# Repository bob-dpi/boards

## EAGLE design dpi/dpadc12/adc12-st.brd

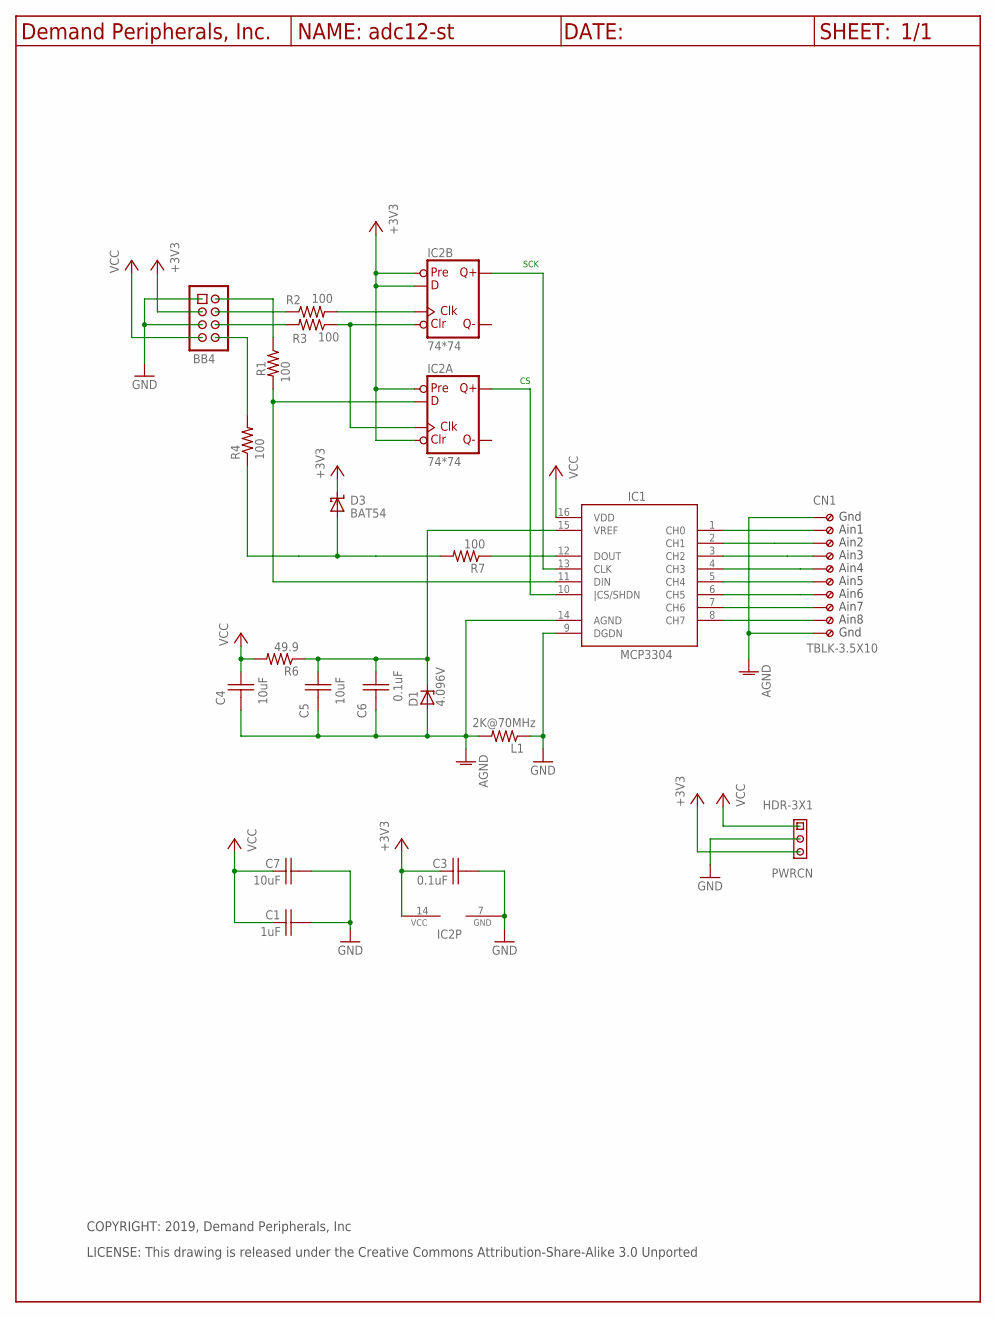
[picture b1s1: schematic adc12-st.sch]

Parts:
BB4: BB4_CON; HDR-4X2
C1: 1uF; C0603
C3, C6: 0.1uF; C0603
C4, C5, C7: 10uF; C0805
CN1: TBLK-3.5X10
D1: 4.096V; SOT23
D3: BAT54; SOT23
IC1: MCP3304; SO16
IC2: 74*74; SO14
L1: 2K@70MHz; R0805
PWRCN: HDR-3X1
R1, R2, R3, R4, R7: 100; R0603
R6: 49.9; R0603
U$3: DP_FRAME_P; LETTER_P

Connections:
+3V3: BB4.3, C3.1, D3.3 (CC), IC2.1 (CLR), IC2.4 (PRE), IC2.10 (PRE), IC2.12 (D), IC2.14 (VCC), PWRCN.3
AGND: C4.2, C5.2, C6.2, CN1.1 (KL), CN1.10 (KL9), D1.2 (A), IC1.14 (AGND), L1.2
GND: BB4.1, BB4.5, C1.2, C3.2, C7.2, IC1.9 (DGDN), IC2.7 (GND), L1.1, PWRCN.2
unnamed: CN1.2 (KL1), IC1.1 (CH0)
unnamed: CN1.3 (KL2), IC1.2 (CH1)
unnamed: CN1.4 (KL3), IC1.3 (CH2)
unnamed: CN1.5 (KL4), IC1.4 (CH3)
unnamed: CN1.6 (KL5), IC1.5 (CH4)
unnamed: CN1.7 (KL6), IC1.6 (CH5)
unnamed: CN1.8 (KL7), IC1.7 (CH6)
unnamed: CN1.9 (KL8), IC1.8 (CH7)
unnamed: IC1.12 (DOUT), R7.1
unnamed: D3.1 (A), R4.1, R7.2
unnamed: IC2.3 (CLK), IC2.13 (CLR), R3.1
unnamed: BB4.4, R2.1
unnamed: IC1.11 (DIN), IC2.2 (D), R1.2
unnamed: IC2.11 (CLK), R2.2
unnamed: IC1.10 (|CS/SHDN), IC2.5 (Q)
unnamed: IC1.13 (CLK), IC2.9 (Q)
unnamed: BB4.6, R3.2
unnamed: BB4.2, R1.1
unnamed: BB4.8, R4.2
unnamed: C5.1, C6.1, D1.1 (C), IC1.15 (VREF), R6.1
VCC: BB4.7, C1.1, C4.1, C7.1, IC1.16 (VDD), PWRCN.1, R6.2

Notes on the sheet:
SCK
COPYRIGHT: 2019, Demand Peripherals, Inc
LICENSE: This drawing is released under the Creative Commons Attribution-Share-Alike 3.0 Unported
Gnd
Ain8
Ain1
Ain2
Ain3
Ain4
Ain5
Ain6
Ain7

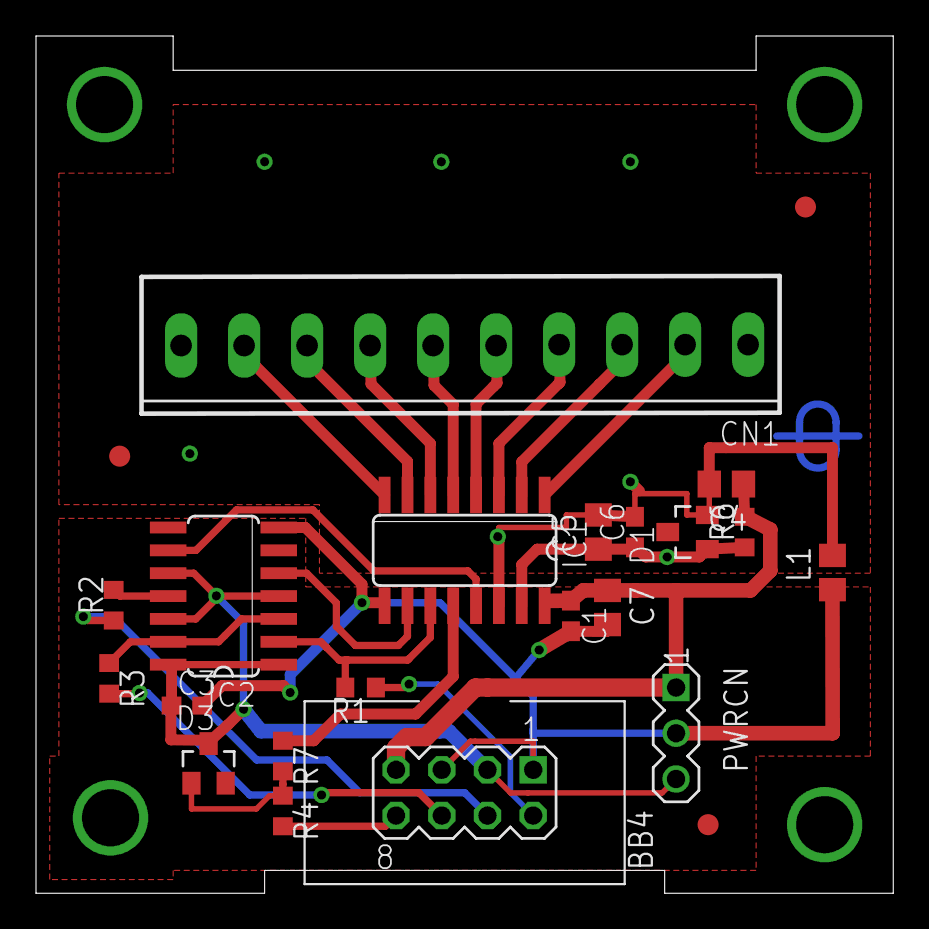
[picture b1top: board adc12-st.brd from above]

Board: 2 copper layers, 47.6 x 47.6 mm, 25 parts (1 on the bottom side), 24 nets.

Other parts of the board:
U$1: DPI-1
U$2, U$5, U$6: FIDUCIAL

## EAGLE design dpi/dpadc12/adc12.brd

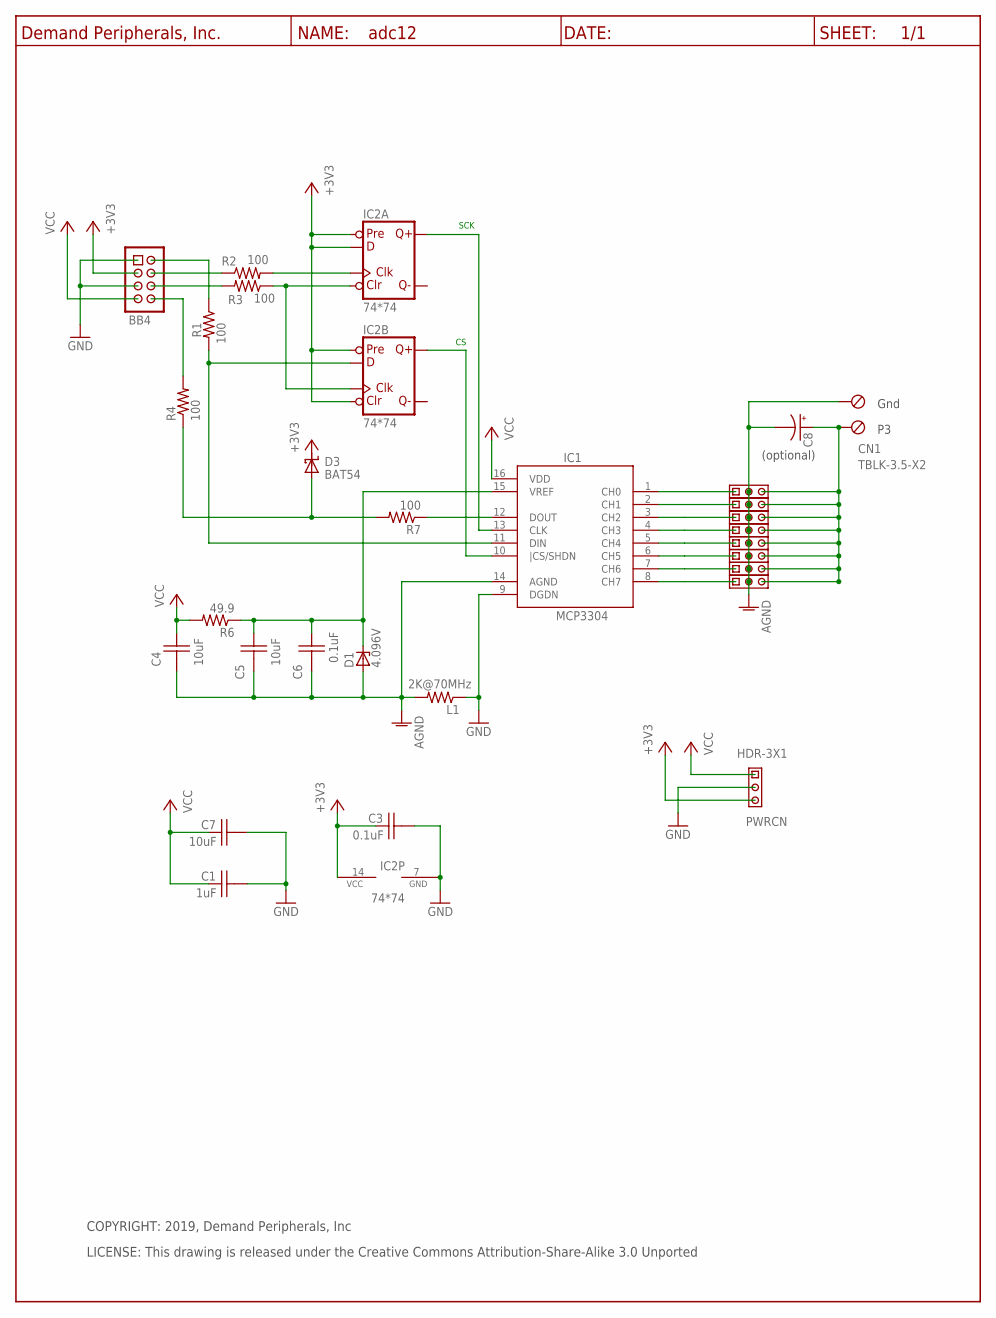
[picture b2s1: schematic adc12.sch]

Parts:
BB4: BB4_CON; HDR-4X2
C1: 1uF; C0603
C3, C6: 0.1uF; C0603
C4, C5, C7: 10uF; C0805
C8: C100UF_E3.5-8; E3.5-8
CN1: TBLK-3.5-X2
D1: 4.096V; SOT23
D3: BAT54; SOT23
IC1: MCP3304; SO16
IC2: 74*74; SO14
L1: 2K@70MHz; R0805
PWRCN: HDR-3X1
R1, R2, R3, R4, R7: 100; R0603
R6: 49.9; R0603
U$3: DP_FRAME_P; LETTER_P
U$6, U$7, U$8, U$9, U$10, U$11, U$12, U$13: HDR-3X1

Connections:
+3V3: BB4.3, C3.1, D3.3 (CC), IC2.2 (D), IC2.4 (PRE), IC2.10 (PRE), IC2.13 (CLR), IC2.14 (VCC), PWRCN.3
AGND: C4.2, C5.2, C6.2, C8.-, CN1.1 (KL), D1.2 (A), IC1.14 (AGND), L1.2, U$6.2, U$7.2, U$8.2, U$9.2, U$10.2, U$11.2, U$12.2, U$13.2
GND: BB4.1, BB4.5, C1.2, C3.2, C7.2, IC1.9 (DGDN), IC2.7 (GND), L1.1, PWRCN.2
unnamed: C8.+, CN1.2 (KL1), U$6.3, U$7.3, U$8.3, U$9.3, U$10.3, U$11.3, U$12.3, U$13.3
unnamed: IC1.2 (CH1), U$12.1
unnamed: IC1.3 (CH2), U$11.1
unnamed: IC1.4 (CH3), U$10.1
unnamed: IC1.5 (CH4), U$9.1
unnamed: IC1.6 (CH5), U$8.1
unnamed: IC1.7 (CH6), U$7.1
unnamed: IC1.8 (CH7), U$6.1
unnamed: IC1.12 (DOUT), R7.1
unnamed: IC1.1 (CH0), U$13.1
unnamed: D3.1 (A), R4.1, R7.2
unnamed: IC2.1 (CLR), IC2.11 (CLK), R3.1
unnamed: BB4.4, R2.1
unnamed: IC1.11 (DIN), IC2.12 (D), R1.2
unnamed: IC2.3 (CLK), R2.2
unnamed: IC1.10 (|CS/SHDN), IC2.9 (Q)
unnamed: IC1.13 (CLK), IC2.5 (Q)
unnamed: BB4.6, R3.2
unnamed: BB4.2, R1.1
unnamed: BB4.8, R4.2
unnamed: C5.1, C6.1, D1.1 (C), IC1.15 (VREF), R6.1
VCC: BB4.7, C1.1, C4.1, C7.1, IC1.16 (VDD), PWRCN.1, R6.2

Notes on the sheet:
SCK
(optional)
Gnd
COPYRIGHT: 2019, Demand Peripherals, Inc
LICENSE: This drawing is released under the Creative Commons Attribution-Share-Alike 3.0 Unported

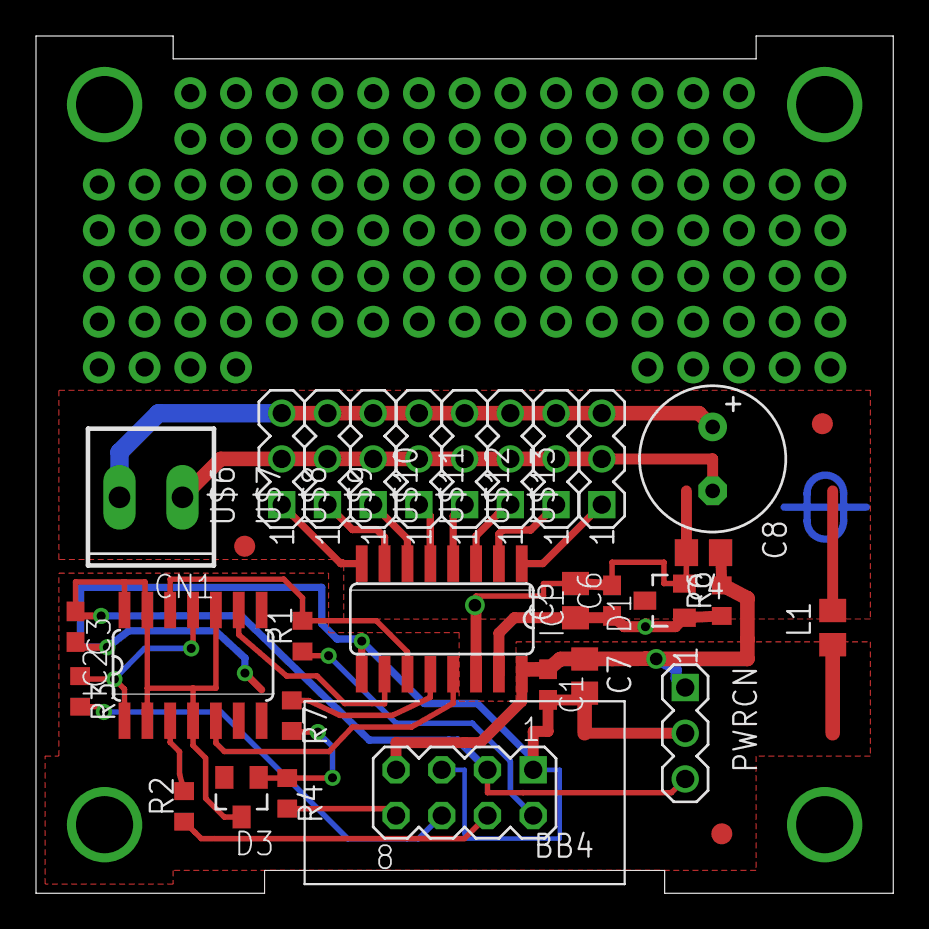
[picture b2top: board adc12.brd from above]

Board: 2 copper layers, 47.6 x 47.6 mm, 34 parts (1 on the bottom side), 25 nets.

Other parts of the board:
U$1: DPI-1
U$2, U$4, U$5: FIDUCIAL

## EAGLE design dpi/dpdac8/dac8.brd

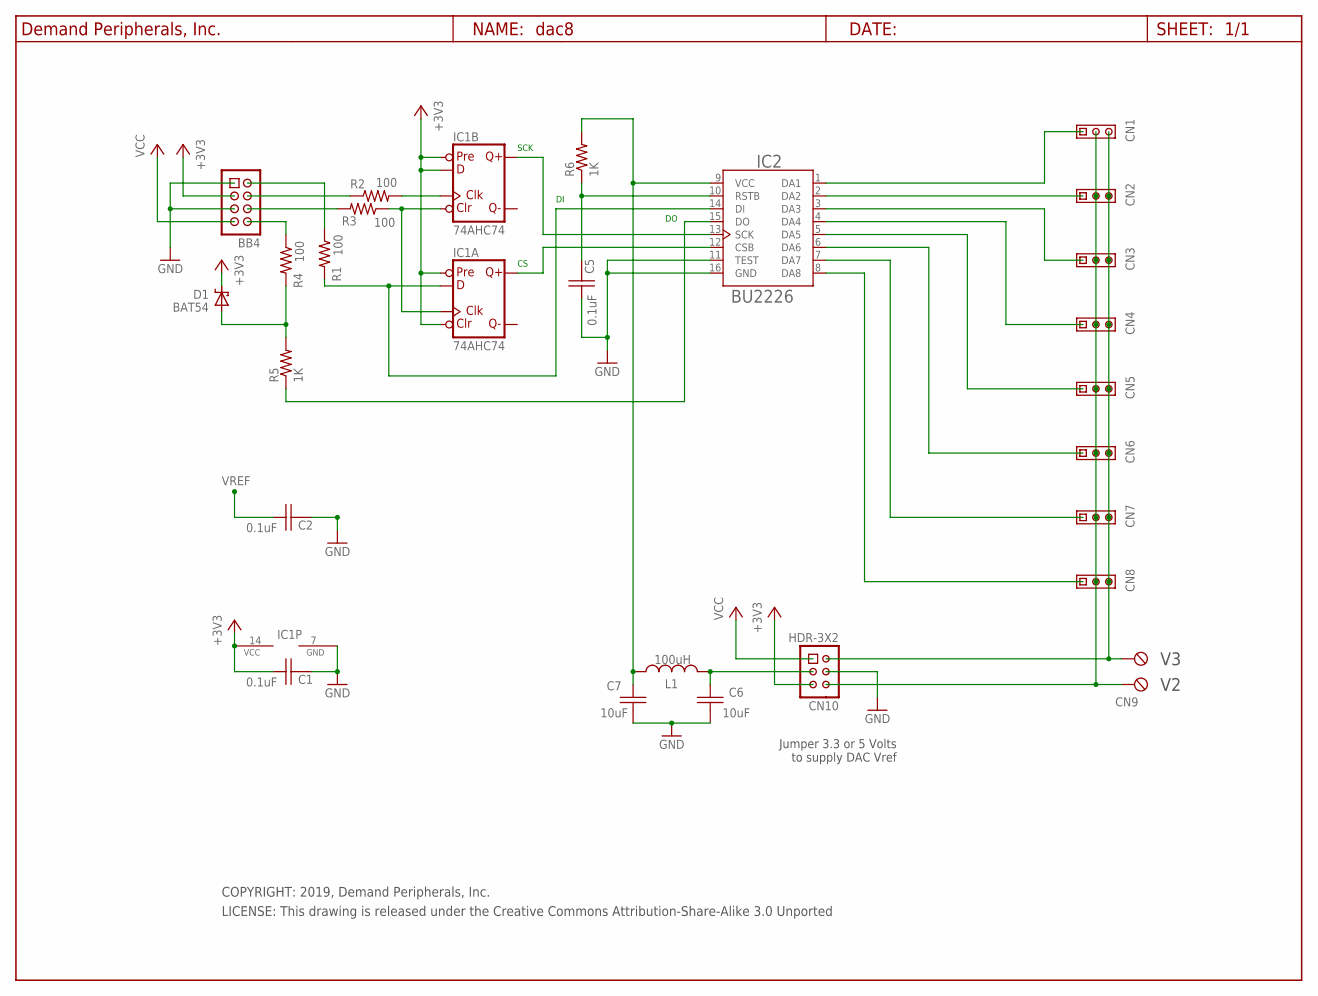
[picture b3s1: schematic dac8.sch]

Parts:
BB4: BB4; HDR-4X2
C1, C2, C5: 0.1uF; C0603
C6, C7: 10uF; C0805
CN1, CN2, CN3, CN4, CN5, CN6, CN7, CN8: HDR-3X1
CN9: TBLK-5.08-X2
CN10: HDR-3X2
D1: BAT54; SOT23
IC1: 74AHC74; SO14
IC2: BU2226; SO16
L1: 100uH; L0805
R1, R2, R3, R4: 100; R0603
R5, R6: 1K; R0603
S1: DP_FRAME_L; L_FRAME

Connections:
+3V3: BB4.3, C1.1, CN10.5, D1.3 (CC), IC1.1 (CLR), IC1.4 (PRE), IC1.10 (PRE), IC1.12 (D), IC1.14 (VCC)
GND: BB4.1, BB4.5, C1.2, C2.2, C5.1, C6.2, C7.2, CN10.4, IC1.7 (GND), IC2.11 (TEST), IC2.16 (GND)
unnamed: IC1.5 (Q), IC2.12 (CSB)
unnamed: IC1.9 (Q), IC2.13 (SCK)
unnamed: CN1.1, IC2.1 (DA1)
unnamed: C5.2, IC2.10 (RSTB), R6.1
unnamed: C6.1, CN10.3, L1.2
unnamed: CN2.1, IC2.2 (DA2)
unnamed: CN3.1, IC2.3 (DA3)
unnamed: CN4.1, IC2.4 (DA4)
unnamed: CN5.1, IC2.5 (DA5)
unnamed: CN6.1, IC2.6 (DA6)
unnamed: CN7.1, IC2.7 (DA7)
unnamed: IC1.3 (CLK), IC1.13 (CLR), R3.1
unnamed: BB4.4, R2.1
unnamed: IC1.2 (D), IC2.14 (DI), R1.2
unnamed: IC1.11 (CLK), R2.2
unnamed: CN8.1, IC2.8 (DA8)
unnamed: D1.1 (A), R4.2, R5.2
unnamed: BB4.6, R3.2
unnamed: BB4.2, R1.1
unnamed: BB4.8, R4.1
unnamed: IC2.15 (DO), R5.1
V2: CN1.2, CN2.2, CN3.2, CN4.2, CN5.2, CN6.2, CN7.2, CN8.2, CN9.1 (KL), CN10.6
V3: CN1.3, CN2.3, CN3.3, CN4.3, CN5.3, CN6.3, CN7.3, CN8.3, CN9.2 (KL1), CN10.2
VCC: BB4.7, CN10.1
VREF: C2.1, C7.1, IC2.9 (VCC), L1.1, R6.2

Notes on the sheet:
SCK
LICENSE: This drawing is released under the Creative Commons Attribution-Share-Alike 3.0 Unported
COPYRIGHT: 2019, Demand Peripherals, Inc.
Jumper 3.3 or 5 Volts to supply DAC Vref

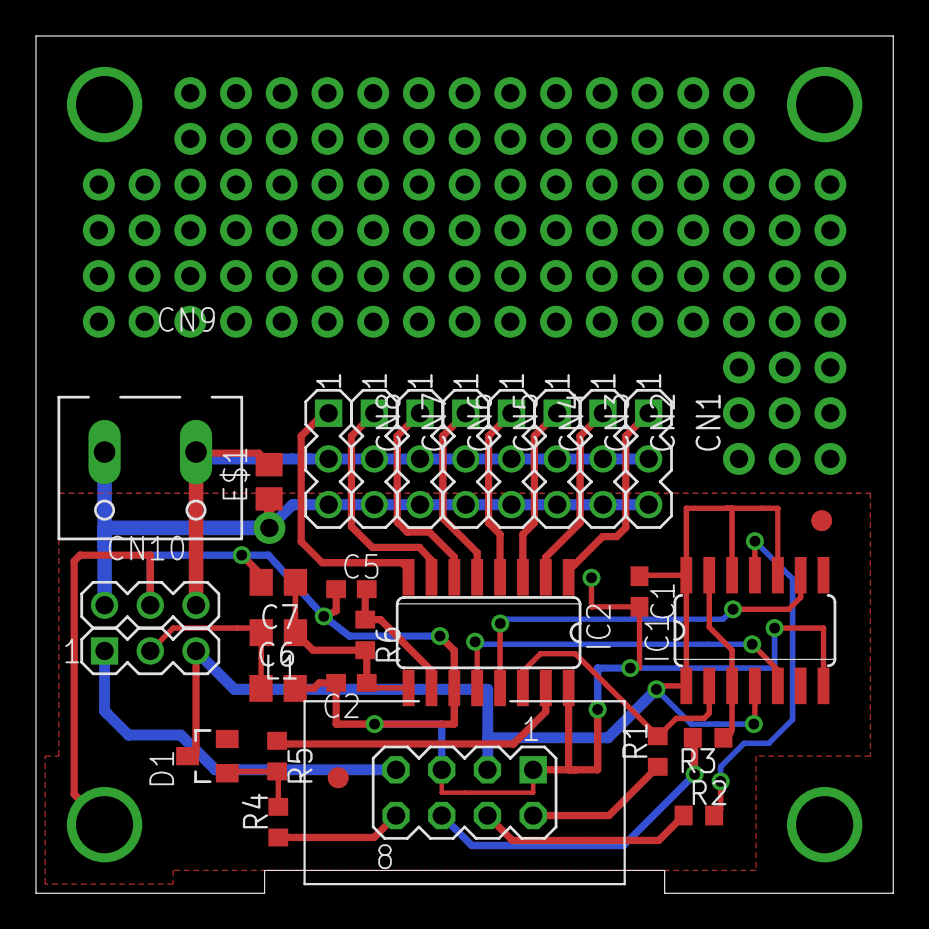
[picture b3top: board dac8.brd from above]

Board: 2 copper layers, 47.6 x 47.6 mm, 31 parts (1 on the bottom side), 27 nets.

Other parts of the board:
E$1: C0805
U$2: DPI-2
U$4, U$6: FIDUCIAL

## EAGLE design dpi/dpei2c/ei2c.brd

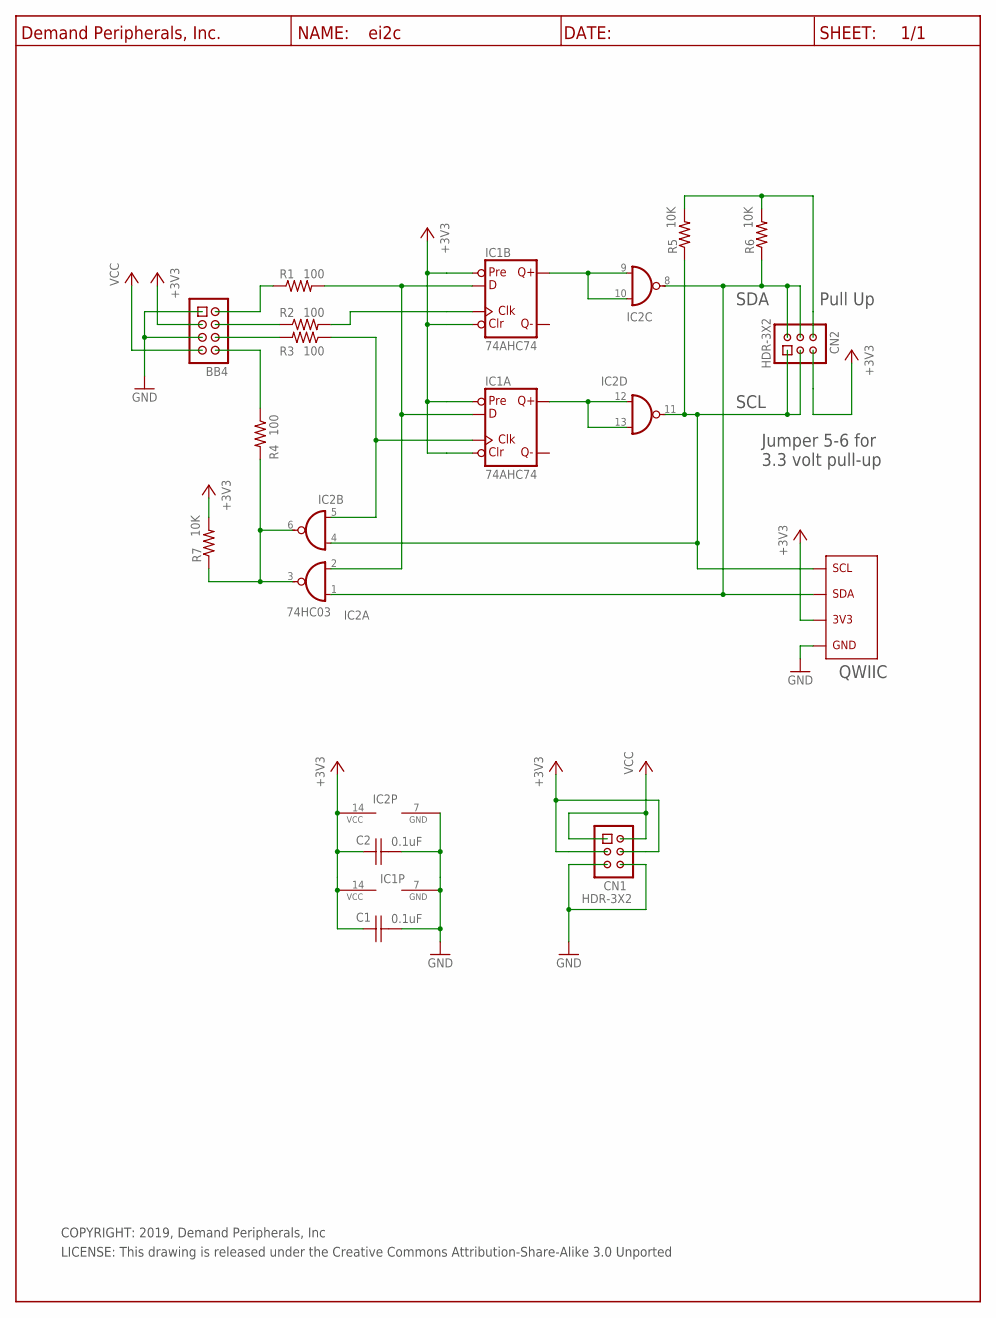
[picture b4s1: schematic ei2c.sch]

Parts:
BB4: BB_CON; HDR-4X2
C1, C2: 0.1uF; C0603
CN1, CN2: HDR-3X2
IC1: 74AHC74; SO14
IC2: 74HC03; SO14
QWIIC: QWIIC-VCN; QWIIC
R1, R2, R3, R4: 100; R0603
R5, R6, R7: 10K; R0603
U$3: DP_FRAME_P; P_FRAME

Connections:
+3V3: BB4.3, C1.1, C2.1, CN1.3, CN1.4, CN2.5, IC1.1 (CLR), IC1.4 (PRE), IC1.10 (PRE), IC1.13 (CLR), IC1.14 (VCC), IC2.14 (VCC), QWIIC.2, R7.2
GND: BB4.1, BB4.5, C1.2, C2.2, CN1.5, CN1.6, IC1.7 (GND), IC2.7 (GND), QWIIC.1
unnamed: IC1.2 (D), IC1.12 (D), IC2.2 (I1), R1.2
unnamed: IC1.9 (Q), IC2.9 (I0), IC2.10 (I1)
unnamed: IC1.5 (Q), IC2.12 (I0), IC2.13 (I1)
unnamed: CN2.2, CN2.4, IC2.1 (I0), IC2.8 (O), QWIIC.3, R6.1
unnamed: CN2.1, CN2.3, IC2.4 (I0), IC2.11 (O), QWIIC.4, R5.1
unnamed: CN2.6, R5.2, R6.2
unnamed: IC2.3 (O), IC2.6 (O), R4.2, R7.1
unnamed: BB4.8, R4.1
unnamed: IC1.3 (CLK), IC2.5 (I1), R3.1
unnamed: BB4.4, R2.1
unnamed: IC1.11 (CLK), R2.2
unnamed: BB4.6, R3.2
unnamed: BB4.2, R1.1
VCC: BB4.7, CN1.1, CN1.2

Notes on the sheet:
Jumper 5-6 for
3.3 volt pull-up
SCL
SDA
Pull Up
COPYRIGHT: 2019, Demand Peripherals, Inc
LICENSE: This drawing is released under the Creative Commons Attribution-Share-Alike 3.0 Unported
QWIIC

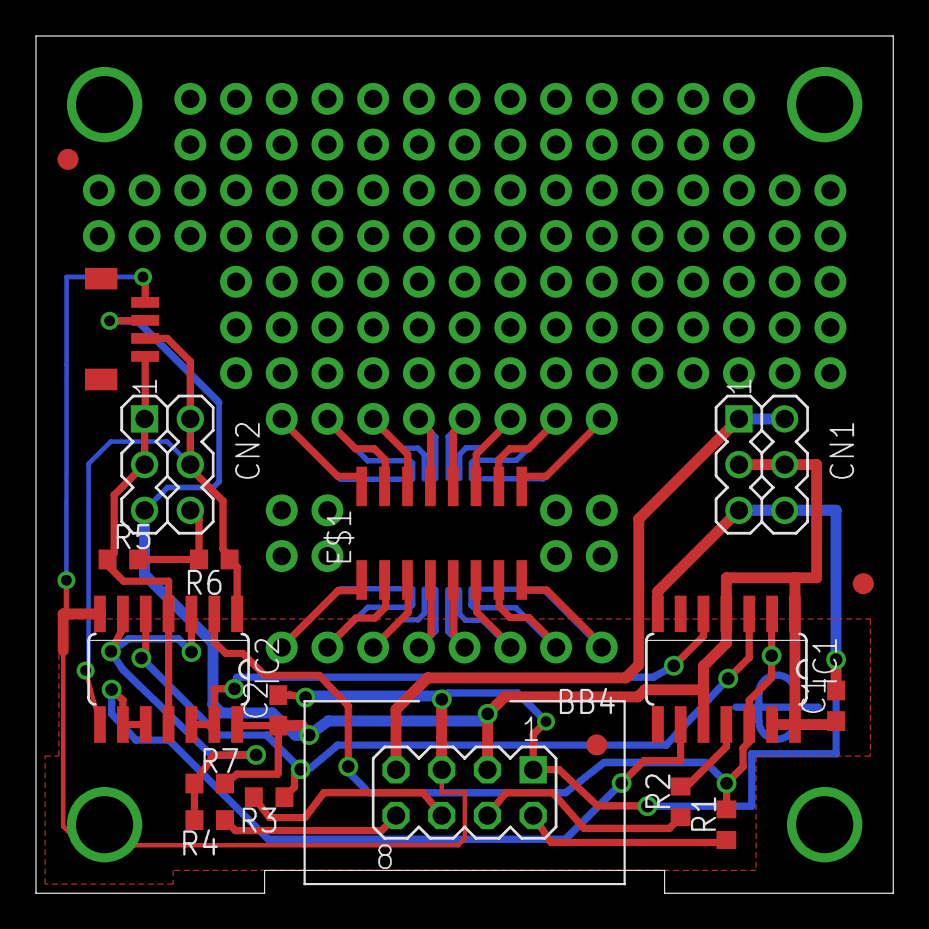
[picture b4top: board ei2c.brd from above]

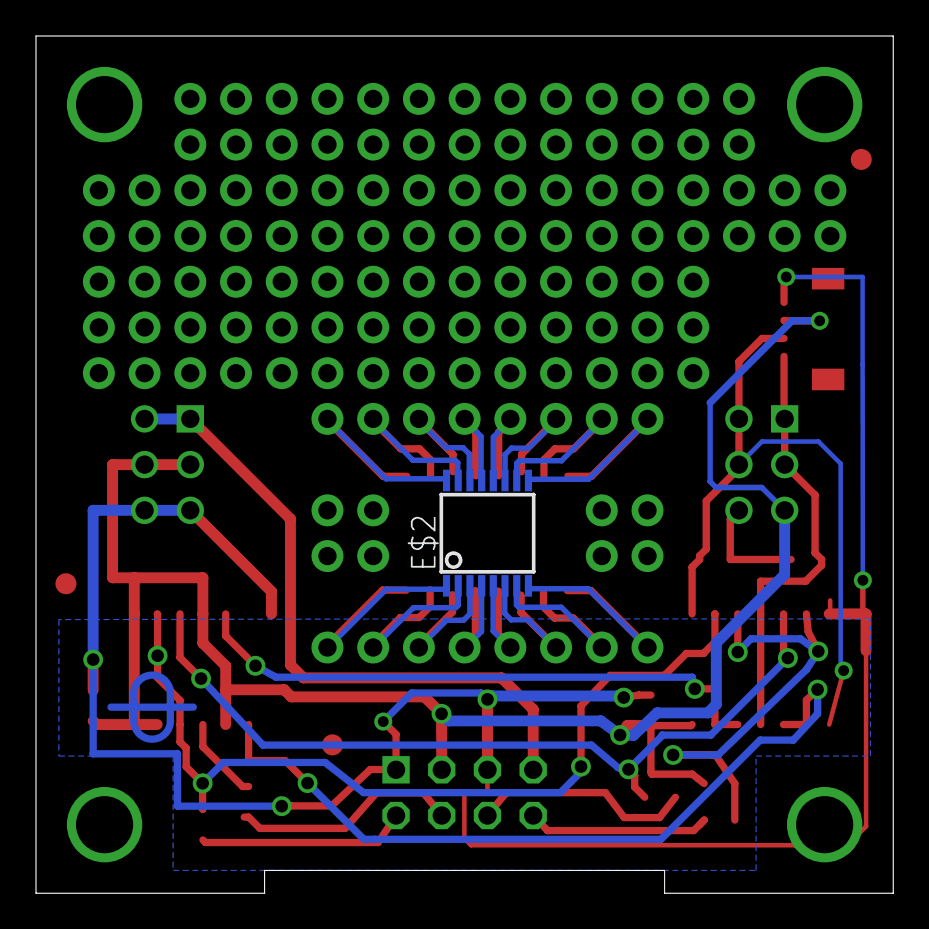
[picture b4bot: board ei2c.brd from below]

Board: 2 copper layers, 47.6 x 47.6 mm, 23 parts (3 on the bottom side), 16 nets.

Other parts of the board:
E$1: SO16
E$2: SSOP16
U$1: DPI-1
U$2, U$4, U$5: FIDUCIAL
U$6: DPI-2

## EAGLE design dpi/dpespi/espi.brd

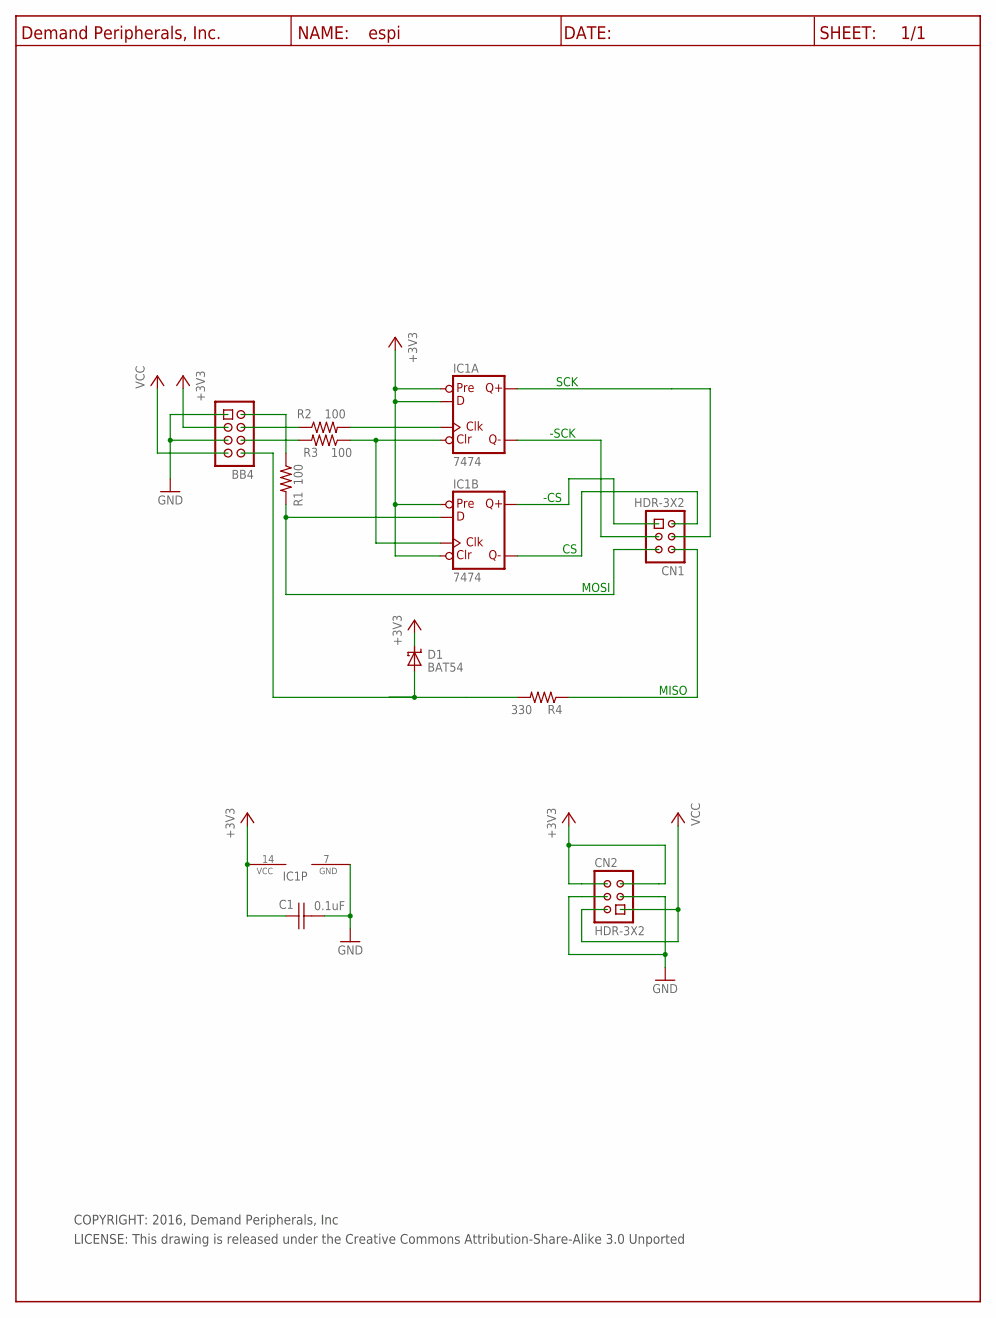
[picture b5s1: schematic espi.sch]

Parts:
BB4: BB_CON; HDR-4X2
C1: 0.1uF; C0603
CN1, CN2: HDR-3X2
D1: BAT54; SOT23
IC1: 7474; SO14
R1, R2, R3: 100; R0603
R4: 330; R0603
U$3: DP_FRAME_P; P_FRAME

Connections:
+3V3: BB4.3, C1.1, CN2.5, CN2.6, D1.3 (CC), IC1.2 (D), IC1.4 (PRE), IC1.10 (PRE), IC1.13 (CLR), IC1.14 (VCC)
GND: BB4.1, BB4.5, C1.2, CN2.3, CN2.4, IC1.7 (GND)
unnamed: CN1.2, IC1.8 (!Q)
unnamed: BB4.8, D1.1 (A), R4.2
unnamed: CN1.1, IC1.9 (Q)
unnamed: CN1.4, IC1.5 (Q)
unnamed: CN1.3, IC1.6 (!Q)
unnamed: CN1.6, R4.1
unnamed: IC1.1 (CLR), IC1.11 (CLK), R3.1
unnamed: BB4.4, R2.1
unnamed: CN1.5, IC1.12 (D), R1.2
unnamed: IC1.3 (CLK), R2.2
unnamed: BB4.6, R3.2
unnamed: BB4.2, R1.1
VCC: BB4.7, CN2.1, CN2.2

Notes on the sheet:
SCK
-SCK
-CS
MOSI
MISO
COPYRIGHT: 2016, Demand Peripherals, Inc
LICENSE: This drawing is released under the Creative Commons Attribution-Share-Alike 3.0 Unported

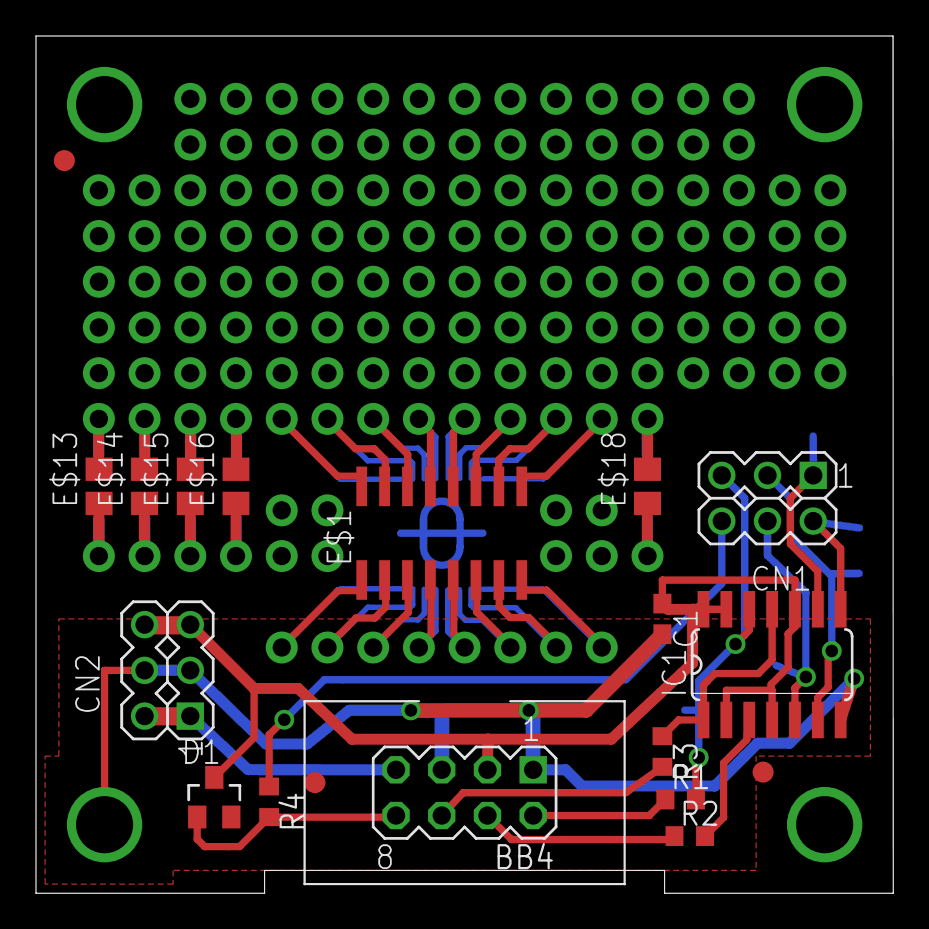
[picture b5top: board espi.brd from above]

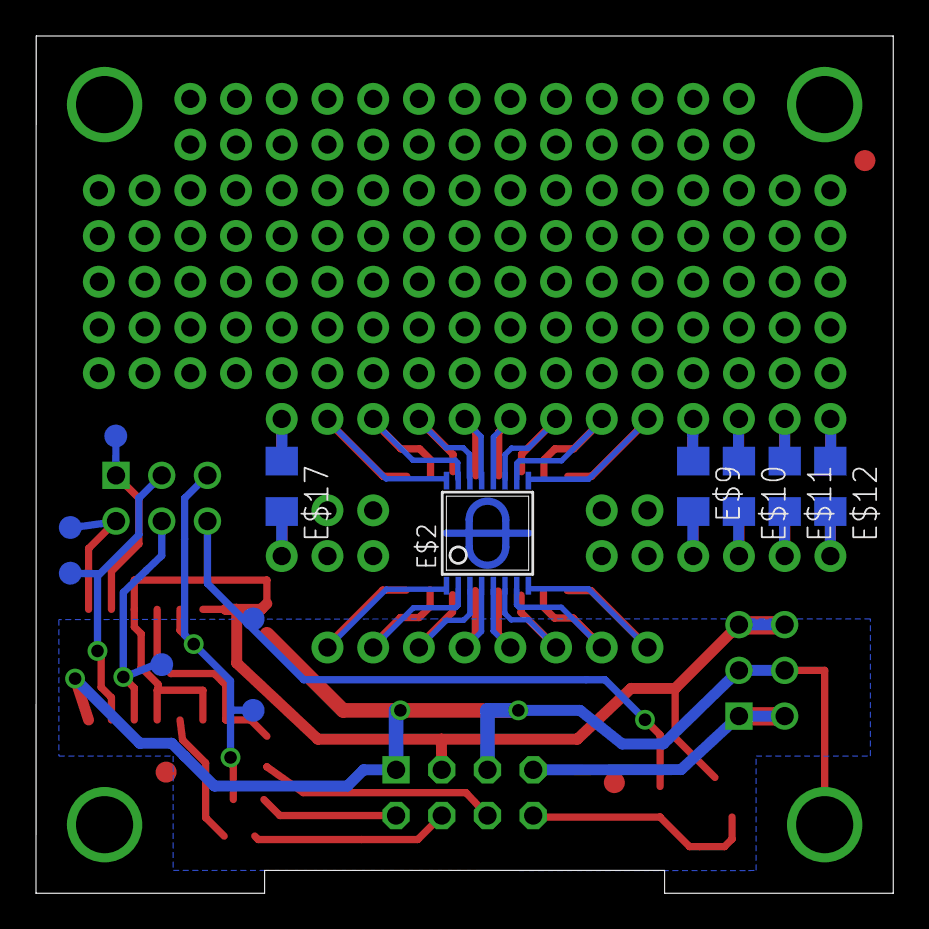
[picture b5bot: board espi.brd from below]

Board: 2 copper layers, 47.6 x 47.6 mm, 33 parts (13 on the bottom side), 15 nets.

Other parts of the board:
E$1: SO16
E$2: TSSOP16
E$3, E$4, E$5, E$6, E$7, E$8: TEST-POINT
E$9, E$10, E$11, E$12, E$17: C1206
E$13, E$14, E$15, E$16, E$18: C0805
U$1: DPI-1
U$4, U$5, U$6: FIDUCIAL

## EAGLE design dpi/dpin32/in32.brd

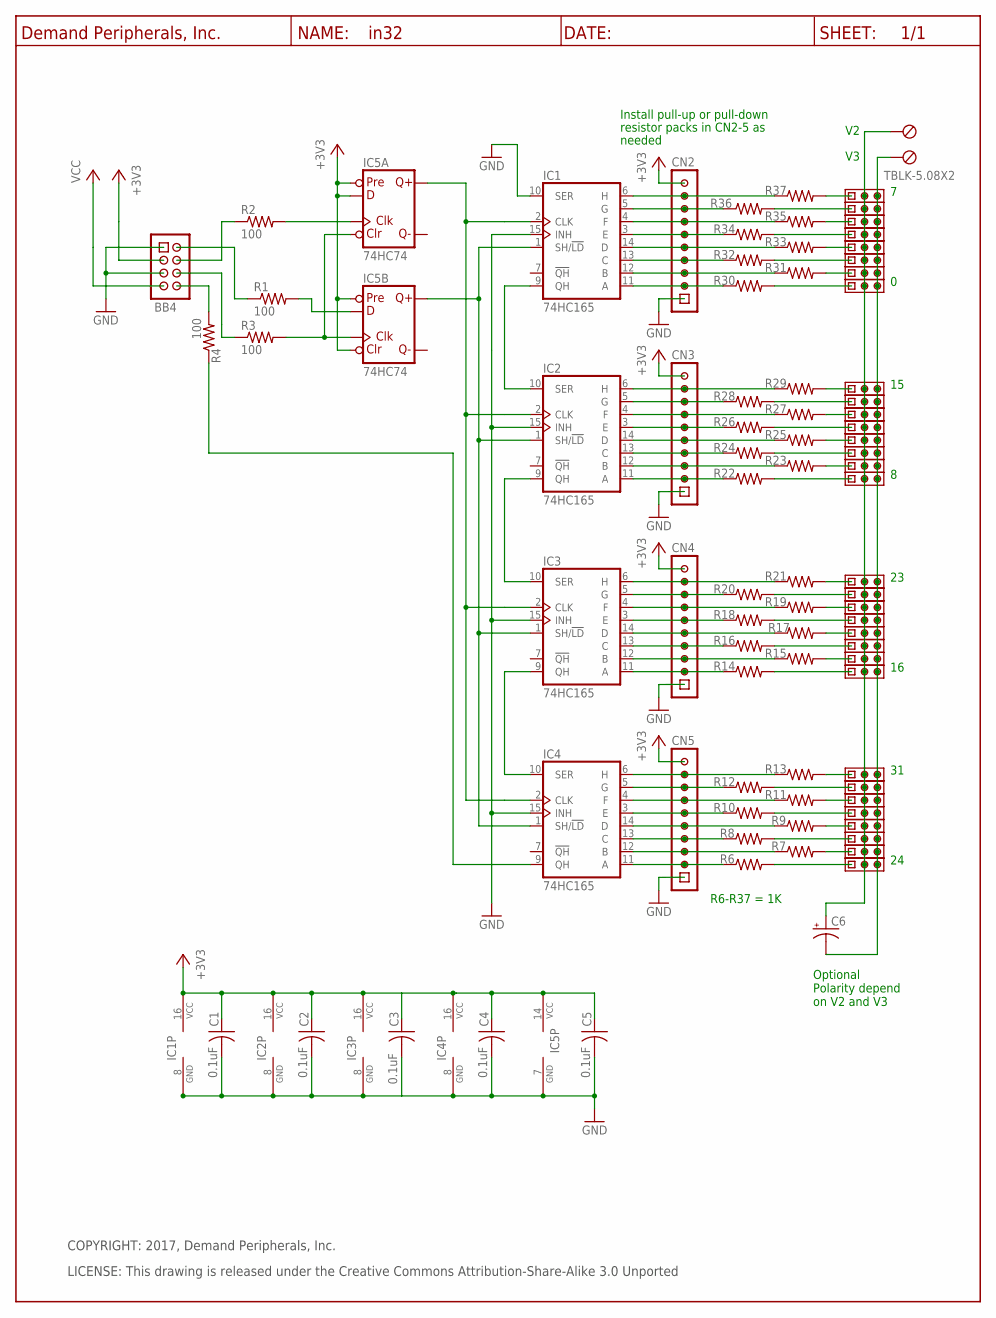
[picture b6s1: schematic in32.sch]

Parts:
BB4: Keyed_Pin_Header_4x2(0.1"x0.1"); HDR-4X2
C1, C2, C3, C4, C5: 0.1uF; C0603
C6: C100UF_E3.5-10; E3.5-10
CN1: TBLK-5.08X2; TBLK-5.08-X2
CN2, CN3, CN4, CN5: HDR-10X1
IC1, IC2, IC3, IC4: 74HC165; SO16
IC5: 74HC74; SO14
R1, R2, R3, R4: 100; R0603
R6, R7, R8, R9, R10, R11, R12, R13, R14, R15, R16, R17, R18, R19, R20, R21, R22, R23, R24, R25, R26, R27, R28, R29, R30, R31, R32, R33, R34, R35, R36, R37: R1K_R0603; R0603
U$2: DP_FRAME_P; P_FRAME
U$8, U$9, U$10, U$11, U$12, U$13, U$14, U$15, U$16, U$17, U$18, U$19, U$20, U$21, U$22, U$23, U$24, U$25, U$26, U$27, U$28, U$29, U$30, U$31, U$32, U$33, U$34, U$35, U$36, U$37, U$38, U$39: HDR-3X1

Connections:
+3V3: BB4.3, C1.1, C2.1, C3.1, C4.1, C5.1, CN2.10, CN3.10, CN4.10, CN5.10, IC1.16 (VCC), IC2.16 (VCC), IC3.16 (VCC), IC4.16 (VCC), IC5.2 (D), IC5.4 (PRE), IC5.10 (PRE), IC5.13 (CLR), IC5.14 (VCC)
GND: BB4.1, BB4.5, C1.2, C2.2, C3.2, C4.2, C5.2, CN2.1, CN3.1, CN4.1, CN5.1, IC1.8 (GND), IC1.10 (SER), IC1.15 (INH), IC2.8 (GND), IC2.15 (INH), IC3.8 (GND), IC3.15 (INH), IC4.8 (GND), IC4.15 (INH), IC5.7 (GND)
unnamed: BB4.8, R4.2
unnamed: CN2.2, IC1.11 (A), R30.1
unnamed: IC1.9 (QH), IC2.10 (SER)
unnamed: IC2.9 (QH), IC3.10 (SER)
unnamed: CN2.3, IC1.12 (B), R31.1
unnamed: CN2.4, IC1.13 (C), R32.1
unnamed: CN2.5, IC1.14 (D), R33.1
unnamed: CN2.6, IC1.3 (E), R34.1
unnamed: CN2.7, IC1.4 (F), R35.1
unnamed: CN2.8, IC1.5 (G), R36.1
unnamed: CN2.9, IC1.6 (H), R37.1
unnamed: CN3.2, IC2.11 (A), R22.1
unnamed: CN3.3, IC2.12 (B), R23.1
unnamed: CN3.4, IC2.13 (C), R24.1
unnamed: CN3.5, IC2.14 (D), R25.1
unnamed: CN3.6, IC2.3 (E), R26.1
unnamed: CN3.7, IC2.4 (F), R27.1
unnamed: CN3.8, IC2.5 (G), R28.1
unnamed: CN3.9, IC2.6 (H), R29.1
unnamed: CN4.2, IC3.11 (A), R14.1
unnamed: CN4.3, IC3.12 (B), R15.1
unnamed: CN4.4, IC3.13 (C), R16.1
unnamed: CN4.5, IC3.14 (D), R17.1
unnamed: CN4.6, IC3.3 (E), R18.1
unnamed: CN4.7, IC3.4 (F), R19.1
unnamed: BB4.2, R1.1
unnamed: CN4.8, IC3.5 (G), R20.1
unnamed: IC5.3 (CLK), R2.2
unnamed: IC3.9 (QH), IC4.10 (SER)
unnamed: IC5.1 (CLR), IC5.11 (CLK), R3.2
unnamed: CN4.9, IC3.6 (H), R21.1
unnamed: BB4.6, R3.1
unnamed: IC1.2 (CLK), IC2.2 (CLK), IC3.2 (CLK), IC4.2 (CLK), IC5.5 (Q)
unnamed: BB4.4, R2.1
unnamed: CN5.2, IC4.11 (A), R6.1
unnamed: IC4.9 (QH), R4.1
unnamed: CN5.3, IC4.12 (B), R7.1
unnamed: CN5.4, IC4.13 (C), R8.1
unnamed: CN5.5, IC4.14 (D), R9.1
unnamed: CN5.6, IC4.3 (E), R10.1
unnamed: CN5.7, IC4.4 (F), R11.1
unnamed: CN5.8, IC4.5 (G), R12.1
unnamed: CN5.9, IC4.6 (H), R13.1
unnamed: R31.2, U$14.1
unnamed: R33.2, U$12.1
unnamed: R35.2, U$10.1
unnamed: IC5.12 (D), R1.2
unnamed: R37.2, U$8.1
unnamed: R23.2, U$22.1
unnamed: R25.2, U$20.1
unnamed: R27.2, U$18.1
unnamed: R29.2, U$16.1
unnamed: R15.2, U$30.1
unnamed: R17.2, U$28.1
unnamed: R19.2, U$26.1
unnamed: R21.2, U$24.1
unnamed: R7.2, U$38.1
unnamed: R9.2, U$36.1
unnamed: R11.2, U$34.1
unnamed: R13.2, U$32.1
unnamed: R36.2, U$9.1
unnamed: R34.2, U$11.1
unnamed: IC1.1 (SH/!LD), IC2.1 (SH/!LD), IC3.1 (SH/!LD), IC4.1 (SH/!LD), IC5.9 (Q)
unnamed: R32.2, U$13.1
unnamed: R30.2, U$15.1
unnamed: R22.2, U$23.1
unnamed: R24.2, U$21.1
unnamed: R26.2, U$19.1
unnamed: R28.2, U$17.1
unnamed: R20.2, U$25.1
unnamed: R18.2, U$27.1
unnamed: R16.2, U$29.1
unnamed: R14.2, U$31.1
unnamed: R6.2, U$39.1
unnamed: R8.2, U$37.1
unnamed: R10.2, U$35.1
unnamed: R12.2, U$33.1
V2: C6.+, CN1.1 (KL), U$8.2, U$9.2, U$10.2, U$11.2, U$12.2, U$13.2, U$14.2, U$15.2, U$16.2, U$17.2, U$18.2, U$19.2, U$20.2, U$21.2, U$22.2, U$23.2, U$24.2, U$25.2, U$26.2, U$27.2, U$28.2, U$29.2, U$30.2, U$31.2, U$32.2, U$33.2, U$34.2, U$35.2, U$36.2, U$37.2, U$38.2, U$39.2
V3: C6.-, CN1.2 (KL1), U$8.3, U$9.3, U$10.3, U$11.3, U$12.3, U$13.3, U$14.3, U$15.3, U$16.3, U$17.3, U$18.3, U$19.3, U$20.3, U$21.3, U$22.3, U$23.3, U$24.3, U$25.3, U$26.3, U$27.3, U$28.3, U$29.3, U$30.3, U$31.3, U$32.3, U$33.3, U$34.3, U$35.3, U$36.3, U$37.3, U$38.3, U$39.3
VCC: BB4.7

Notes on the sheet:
COPYRIGHT: 2017, Demand Peripherals, Inc.
LICENSE: This drawing is released under the Creative Commons Attribution-Share-Alike 3.0 Unported
Install pull-up or pull-down
resistor packs in CN2-5 as
needed
R6-R37 = 1K
Optional Polarity depend on V2 and V3

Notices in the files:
dpi/dpadc12/adc12-st.brd:
(C) 2019, Demand Peripherals, Inc.
dpi/dpin32/in32.brd:
(C) 2018, Demand Peripherals, Inc.
dpi/dpio8/io8.brd:
(C) 2017, Demand Peripherals, Inc.
